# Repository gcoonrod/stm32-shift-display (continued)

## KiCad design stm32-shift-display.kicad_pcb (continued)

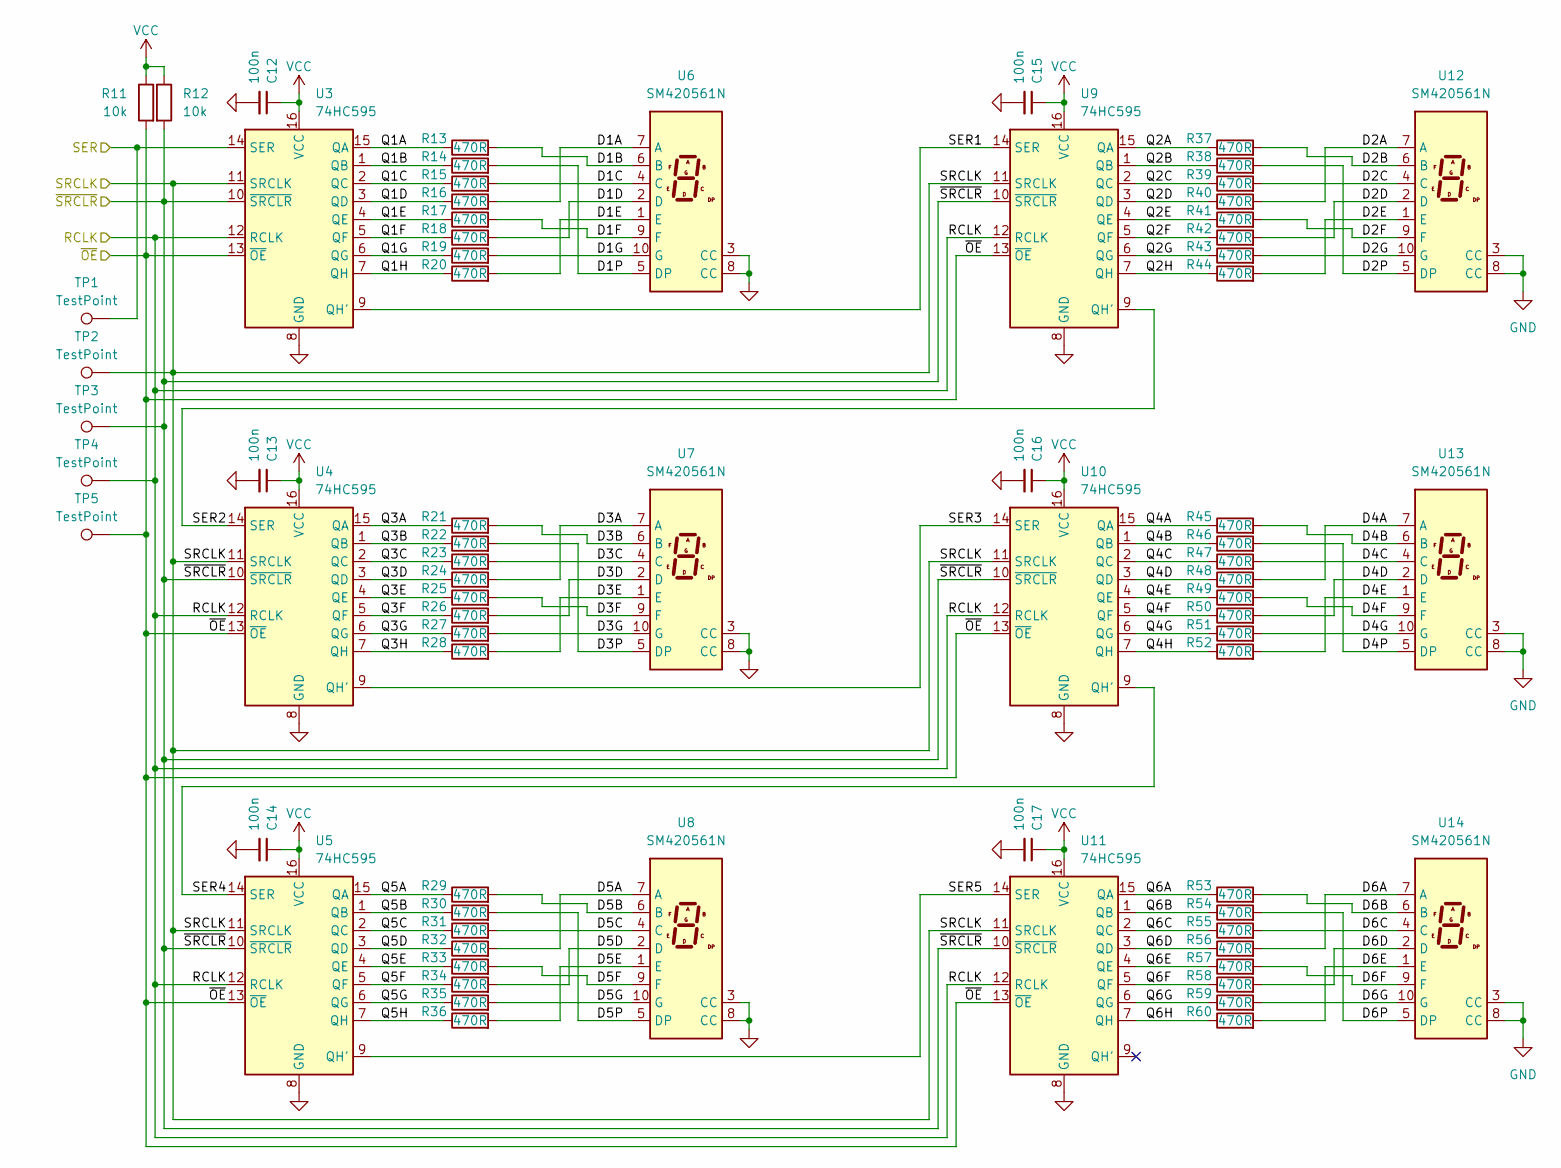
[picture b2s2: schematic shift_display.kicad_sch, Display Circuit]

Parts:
C12, C13, C14, C15, C16, C17: 100n; C_0402_1005Metric; MFR Part CL05B104KB54PNC; JLCPCB Part C307331
R11, R12: 10k; R_0402_1005Metric; JLCPCB Part C25744
R13, R14, R15, R16, R17, R18, R19, R20, R21, R22, R23, R24, R25, R26, R27, R28, R29, R30, R31, R32, R33, R34, R35, R36, R37, R38, R39, R40, R41, R42, R43, R44, R45, R46, R47, R48, R49, R50, R51, R52, R53, R54, R55, R56, R57, R58, R59, R60: 470R; R_0603_1608Metric; JLCPCB Part C23179
TP1, TP2, TP3, TP4, TP5: TestPoint; TestPoint_Pad_D1.5mm
U3, U4, U5, U9, U10, U11: 74HC595; SOIC-16_3.9x9.9mm_P1.27mm; JLCPCB Part C5947
U6, U7, U8, U12, U13, U14: SM420561N; 7SegmentLED_LTS6760_LTS6780; MFR Part 157142B12703; Mouser Part 710-157142B12703

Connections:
/Shift Display/D1A: R16.2, U6.7 (A)
/Shift Display/D1B: R13.2, U6.6 (B)
/Shift Display/D1C: R15.2, U6.4 (C)
/Shift Display/D1D: R18.2, U6.2 (D)
/Shift Display/D1E: R20.2, U6.1 (E)
/Shift Display/D1F: R17.2, U6.9 (F)
/Shift Display/D1G: R19.2, U6.10 (G)
/Shift Display/D1P: R14.2, U6.5 (DP)
/Shift Display/D2A: R40.2, U12.7 (A)
/Shift Display/D2B: R37.2, U12.6 (B)
/Shift Display/D2C: R39.2, U12.4 (C)
/Shift Display/D2D: R42.2, U12.2 (D)
/Shift Display/D2E: R44.2, U12.1 (E)
/Shift Display/D2F: R41.2, U12.9 (F)
/Shift Display/D2G: R43.2, U12.10 (G)
/Shift Display/D2P: R38.2, U12.5 (DP)
/Shift Display/D3A: R24.2, U7.7 (A)
/Shift Display/D3B: R21.2, U7.6 (B)
/Shift Display/D3C: R23.2, U7.4 (C)
/Shift Display/D3D: R26.2, U7.2 (D)
/Shift Display/D3E: R28.2, U7.1 (E)
/Shift Display/D3F: R25.2, U7.9 (F)
/Shift Display/D3G: R27.2, U7.10 (G)
/Shift Display/D3P: R22.2, U7.5 (DP)
/Shift Display/D4A: R48.2, U13.7 (A)
/Shift Display/D4B: R45.2, U13.6 (B)
/Shift Display/D4C: R47.2, U13.4 (C)
/Shift Display/D4D: R50.2, U13.2 (D)
/Shift Display/D4E: R52.2, U13.1 (E)
/Shift Display/D4F: R49.2, U13.9 (F)
/Shift Display/D4G: R51.2, U13.10 (G)
/Shift Display/D4P: R46.2, U13.5 (DP)
/Shift Display/D5A: R32.2, U8.7 (A)
/Shift Display/D5B: R29.2, U8.6 (B)
/Shift Display/D5C: R31.2, U8.4 (C)
/Shift Display/D5D: R34.2, U8.2 (D)
/Shift Display/D5E: R36.2, U8.1 (E)
/Shift Display/D5F: R33.2, U8.9 (F)
/Shift Display/D5G: R35.2, U8.10 (G)
/Shift Display/D5P: R30.2, U8.5 (DP)
/Shift Display/D6A: R56.2, U14.7 (A)
/Shift Display/D6B: R53.2, U14.6 (B)
/Shift Display/D6C: R55.2, U14.4 (C)
/Shift Display/D6D: R58.2, U14.2 (D)
/Shift Display/D6E: R60.2, U14.1 (E)
/Shift Display/D6F: R57.2, U14.9 (F)
/Shift Display/D6G: R59.2, U14.10 (G)
/Shift Display/D6P: R54.2, U14.5 (DP)
/Shift Display/Q1A: R13.1, U3.15 (QA)
/Shift Display/Q1B: R14.1, U3.1 (QB)
/Shift Display/Q1C: R15.1, U3.2 (QC)
/Shift Display/Q1D: R16.1, U3.3 (QD)
/Shift Display/Q1E: R17.1, U3.4 (QE)
/Shift Display/Q1F: R18.1, U3.5 (QF)
/Shift Display/Q1G: R19.1, U3.6 (QG)
/Shift Display/Q1H: R20.1, U3.7 (QH)
/Shift Display/Q2A: R37.1, U9.15 (QA)
/Shift Display/Q2B: R38.1, U9.1 (QB)
/Shift Display/Q2C: R39.1, U9.2 (QC)
/Shift Display/Q2D: R40.1, U9.3 (QD)
/Shift Display/Q2E: R41.1, U9.4 (QE)
/Shift Display/Q2F: R42.1, U9.5 (QF)
/Shift Display/Q2G: R43.1, U9.6 (QG)
/Shift Display/Q2H: R44.1, U9.7 (QH)
/Shift Display/Q3A: R21.1, U4.15 (QA)
/Shift Display/Q3B: R22.1, U4.1 (QB)
/Shift Display/Q3C: R23.1, U4.2 (QC)
/Shift Display/Q3D: R24.1, U4.3 (QD)
/Shift Display/Q3E: R25.1, U4.4 (QE)
/Shift Display/Q3F: R26.1, U4.5 (QF)
/Shift Display/Q3G: R27.1, U4.6 (QG)
/Shift Display/Q3H: R28.1, U4.7 (QH)
/Shift Display/Q4A: R45.1, U10.15 (QA)
/Shift Display/Q4B: R46.1, U10.1 (QB)
/Shift Display/Q4C: R47.1, U10.2 (QC)
/Shift Display/Q4D: R48.1, U10.3 (QD)
/Shift Display/Q4E: R49.1, U10.4 (QE)
/Shift Display/Q4F: R50.1, U10.5 (QF)
/Shift Display/Q4G: R51.1, U10.6 (QG)
/Shift Display/Q4H: R52.1, U10.7 (QH)
/Shift Display/Q5A: R29.1, U5.15 (QA)
/Shift Display/Q5B: R30.1, U5.1 (QB)
/Shift Display/Q5C: R31.1, U5.2 (QC)
/Shift Display/Q5D: R32.1, U5.3 (QD)
/Shift Display/Q5E: R33.1, U5.4 (QE)
/Shift Display/Q5F: R34.1, U5.5 (QF)
/Shift Display/Q5G: R35.1, U5.6 (QG)
/Shift Display/Q5H: R36.1, U5.7 (QH)
/Shift Display/Q6A: R53.1, U11.15 (QA)
/Shift Display/Q6B: R54.1, U11.1 (QB)
/Shift Display/Q6C: R55.1, U11.2 (QC)
/Shift Display/Q6D: R56.1, U11.3 (QD)
/Shift Display/Q6E: R57.1, U11.4 (QE)
/Shift Display/Q6F: R58.1, U11.5 (QF)
/Shift Display/Q6G: R59.1, U11.6 (QG)
/Shift Display/Q6H: R60.1, U11.7 (QH)
/Shift Display/RCLK: TP4.1, U3.12 (RCLK), U4.12 (RCLK), U5.12 (RCLK), U9.12 (RCLK), U10.12 (RCLK), U11.12 (RCLK); also elsewhere on the board
/Shift Display/SER: TP1.1, U3.14 (SER); also elsewhere on the board
/Shift Display/SER1: U3.9 (QH'), U9.14 (SER)
/Shift Display/SER2: U4.14 (SER), U9.9 (QH')
/Shift Display/SER3: U4.9 (QH'), U10.14 (SER)
/Shift Display/SER4: U5.14 (SER), U10.9 (QH')
/Shift Display/SER5: U5.9 (QH'), U11.14 (SER)
/Shift Display/SRCLK: TP2.1, U3.11 (SRCLK), U4.11 (SRCLK), U5.11 (SRCLK), U9.11 (SRCLK), U10.11 (SRCLK), U11.11 (SRCLK); also elsewhere on the board
/Shift Display/~OE: R11.2, TP5.1, U3.13 (~OE), U4.13 (~OE), U5.13 (~OE), U9.13 (~OE), U10.13 (~OE), U11.13 (~OE); also elsewhere on the board
/Shift Display/~SRCLR: R12.2, TP3.1, U3.10 (~SRCLR), U4.10 (~SRCLR), U5.10 (~SRCLR), U9.10 (~SRCLR), U10.10 (~SRCLR), U11.10 (~SRCLR); also elsewhere on the board
GND: C12.2, C13.2, C14.2, C15.2, C16.2, C17.2, U3.8 (GND), U4.8 (GND), U5.8 (GND), U6.3 (CC), U6.8 (CC), U7.3 (CC), U7.8 (CC), U8.3 (CC), U8.8 (CC), U9.8 (GND), U10.8 (GND), U11.8 (GND), U12.3 (CC), U12.8 (CC), U13.3 (CC), U13.8 (CC), U14.3 (CC), U14.8 (CC); also elsewhere on the board
VCC: C12.1, C13.1, C14.1, C15.1, C16.1, C17.1, R11.1, R12.1, U3.16 (VCC), U4.16 (VCC), U5.16 (VCC), U9.16 (VCC), U10.16 (VCC), U11.16 (VCC); also elsewhere on the board

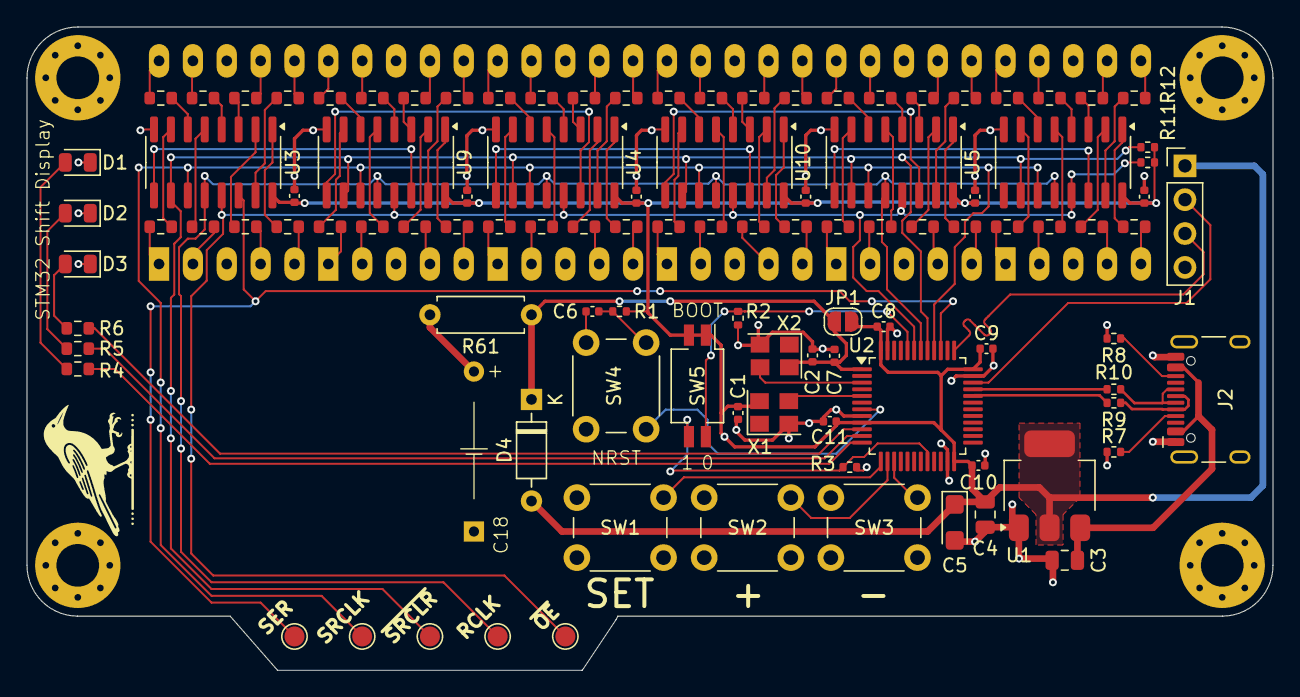
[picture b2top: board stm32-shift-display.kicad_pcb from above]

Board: 2 copper layers, 93.5 x 48.3 mm, 116 parts (0 on the bottom side), 133 nets.

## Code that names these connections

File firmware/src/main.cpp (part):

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
using namespace ace_button;

#define SER PA3
#define SRCLK PA4
#define SRCLRB PA1
#define RCLK PA2
#define OEB PA0

/**
 * ~OE must not be one of the shift-register control pins, and none of them may
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 * that they run opposite to the schematic's D-numbering, which is a trap worth
 * keeping in mind when cross-referencing:
 *
 *   LED_TOP  PB8  net /LED3  schematic D3  -> AM indicator (12-hour mode only)
 *   LED_MID  PB7  net /LED2  schematic D2  -> 12-hour mode active
 *   LED_BOT  PB6  net /LED1  schematic D1  -> alarm armed (steady) / firing (blink)
 *
 * All three are active high: the cathodes tie to GND through their resistors.
 */
#define LED_BOT PB6
#define LED_MID PB7
#define LED_TOP PB8
#define BTN_SET PB5
#define BTN_PLUS PB4
#define BTN_MINUS PB3

// Utility types
enum ButtonState
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}

/**
 * The indicators are PWM-driven, not switched. PB6/PB7/PB8 are TIM4_CH1/CH2/CH3,
 * which analogWrite() resolves through PinMap_TIM without this code naming the
 * timer; the core's defaults are 8-bit duty at 1 kHz.
 *
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
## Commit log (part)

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2024-05-30 initial commit and board rev 0
2024-05-30 Add license, readme, and file moves.
2024-06-01 add initial development firmware
2024-06-01 Add DP control
2024-06-01 Add basic clock display
2024-06-02 Switch to rtc for clock
2024-06-05 Update firmware for board rev 0
2024-06-06 Store date time in variable
2024-06-06 Update platformio config to match rev0 and enable debug.
2024-06-21 Pre-autoroute on rev2
2024-06-22 Initial rev2 design, layout, routing, and mech done. Order submitted.
2024-07-09 documentation updates
2024-07-12 minor firmware changes
2024-07-12 Changes to support rev2 board.
2024-07-12 Fix DP bit mask
2024-07-12 kicad project updates
2024-07-14 Add basic USB serial commands to set time.
2024-07-17 Update readme with media.
2024-07-17 formatting
2024-07-18 add additional assets
2024-10-18 add gitignore
